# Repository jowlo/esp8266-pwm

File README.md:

# **esp8266-pwm** #
This is only a fork. Everything below is the the original repository's README by [lexszero](https://github.com/lexszero/). It will be kept here until I get around rewriting (parts of) it.
The main goal of this fork is to support multiple PCA9685s on one I2C-line as well as not using MQTT but (if the ESP8266 can handle it) WebSockets for use by a client

All changes to the code and effectively this repository as a whole is under [GPL](https://www.gnu.org/licenses/gpl.txt), whereas lexszeros original code is under WTFPL license (see below).
If i understand the licensing laws correctly, it is allowed to incorporate code released to the Public Domain in... tl;dr. If you disagree, please tell me.)

# Original Readme

## Summary
Code for ESP8266 WiFi module with [NodeMcu firmware](https://github.com/nodemcu/nodemcu-firmware) to control PCA9685 PWM controller. You can easily build WiFi-controlled smart home equipment or toys with this. Also contains a demo application: RGB LED strip with WiFi.

Licensed under [WTFPL](http://www.wtfpl.net/)

## Requirements
### Hardware
- Any ESP8266 module
- PCA9685 connected to ESP's GPIOs

My hardware (so mad skillz!):

_TODO: example schematics, photo/video of actual hardware_

### Software
- [NodeMCU](https://github.com/nodemcu/nodemcu-firmware)
- [esptool](https://github.com/themadinventor/esptool) for flashing NodeMCU
- [luatool](https://github.com/4refr0nt/luatool) for uploading Lua code

## PCA9685 driver Lua API
~~TODO: maybe write something useful here~~

Read the source

There are also some useful stuff in `utils.lua`

## rgbstrip: demo application
Directory `rgbstrip` contains an application to control a RGB LED strip over WiFi via [MQTT protocol](https://en.wikipedia.org/wiki/MQTT). RGB channels are usually driven with MOSFETs controlled by PWM.

### Installation
- Connect ESP8266 to PC (we assume that device is connected to `/dev/ttyUSB0`)
- Install `NodeMCU`, if you don't have one:
```
./esptool/esptool.py --port /dev/ttyUSB0 erase_flash
./esptool/esptool.py --port /dev/ttyUSB0 write_flash 0x0 nodemcu-firmware/pre_build/latest/nodemcu_latest.bin
```
- Edit `rgbstrip/init.lua` and change configuration as you wish
- Upload Lua files
```
for f in pca9685.lua rgbstrip/*.lua; do
    ./luatool/luatool.py -f "$f" -t "`basename $f`" -p /dev/ttyUSB0 || break
done
```
- Pre-compile `pca9685.lua` and `server.lua` on ESP8266. This is needed because `NodeMCU` sometimes runs out of RAM when loading Lua modules. Open your favorite serial terminal program (**warning**: `init.lua` configures UART to 115200 baud, `NodeMCU`'s default is 9600). Run following commands in `NodeMCU` REPL:
```
node.compile('pca9685.lua')
node.compile('server.lua')
```
- If there was a compilation error, you can reset device and try again. Shit happens.
- If compilation was succesfull, there will be created `pca9685.lc` and `server.lc` files in `NodeMCU` filesystem. Now original files can be removed:
```
file.remove('pca9685.lua')
file.remove('server.lua')
```

### MQTT interface
To control RGB strip, publish a MQTT message with topic `<mqtt_topic>/rgb` (where `<mqtt_topic>` is what you set in `init.lua`) and payload with desired color as hex string (e.g. `ff00ff` - purple).

### rgbstrip.sh: a simple control tool
It uses [mosquitto](http://mosquitto.org/) to publish MQTT messages and Xdialog for  simple GUI.
* Set your MQTT credentials in `mqtt_args` variable in the beggining of the script
* Run `rgbstrip.sh` with one of the following arguments
	* `w` or `white`: set total brightness (r=g=b)
	* `c` or `color`: set color with regular color choose dialog
	* `h` or `hsvcolor`: set color with Hue/Saturation/Value sliders
	* `m` or `midi`: read MIDI control events from ALSA and set color accordingly
	* any other value: set color with Red/Green/Blue sliders

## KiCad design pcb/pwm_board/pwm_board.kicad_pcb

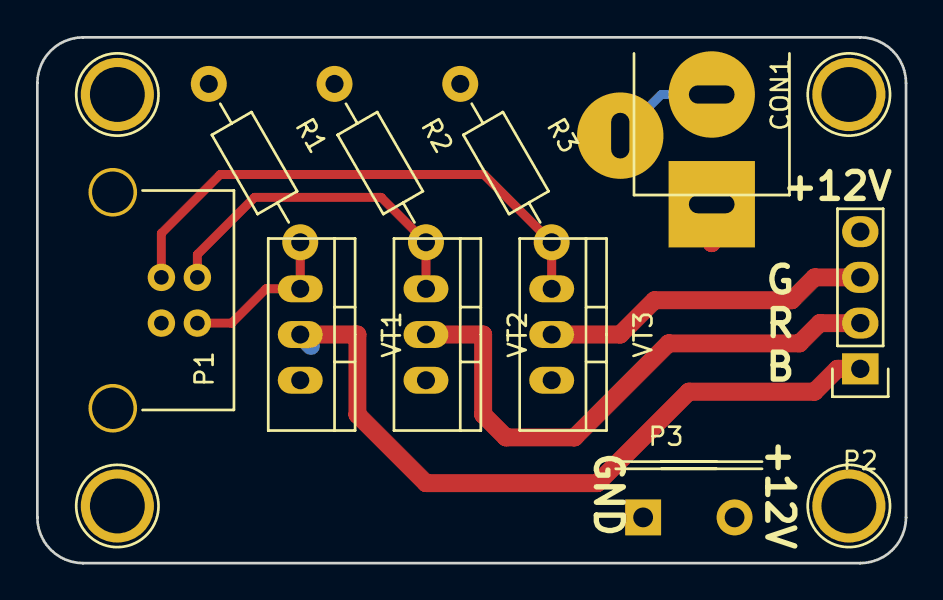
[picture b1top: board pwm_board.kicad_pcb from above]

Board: 2 copper layers, 48.3 x 29.2 mm, 10 parts (0 on the bottom side), 8 nets.

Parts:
CON1: BARREL_JACK; JACK_ALIM
P1: USB_B
P2: CONN_01X04; Pin_Header_Straight_1x04
P3: CONN_01X02; TerminalBlock_Pheonix_MPT-2.54mm_2pol
R1, R2, R3: 10k; Resistor_Horizontal_RM10mm
VT1, VT2, VT3: IRLZ44; TO-220_Neutral123_Vertical

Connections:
Earth: CON1.2, CON1.3, P1.4, P1.5, P3.1, R1.1, R2.1, R3.1, VT1.3, VT2.3, VT3.3
unnamed: CON1.1, P2.4, P3.2
unnamed: P1.1, R1.2, VT1.1
unnamed: P1.2, R2.2, VT2.1
unnamed: P1.3, R3.2, VT3.1
unnamed: P2.1, VT1.2
unnamed: P2.2, VT2.2
unnamed: P2.3, VT3.2

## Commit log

2015-09-22 comments, (try to) optimize i2c-communication, start working on supporting multiple pca9685
2015-09-22 add brightness control
2015-09-24 first working fft
2015-09-24 i guess it works
2015-09-25 adding udpsend
2015-09-25 lots
2015-09-25 pwms and all that
2015-09-25 less noisy terminals
2015-09-25 cleanup
2015-09-26 work on protocol. add 2byte cmd flag. pwm values now 10bit, not 8.
2015-09-28 use native firmware. nodemcu too laggy
2015-09-28 well, there goes my wifi pass. dont try, new one created
2015-09-28 use config.h
2015-09-28 adding settings
2015-10-01 shell
2015-10-01 rename
2015-10-01 file struct cleanup
2015-10-02 gtk gui
2015-10-04 clean working dir
2015-10-04 multi channels
2015-10-04 multiglow
2015-10-04 make flicker work
2015-10-10 start using pca9685 boards
2016-01-02 add python script.
2016-01-03 working python fft. need to logscale binning
2016-01-04 working easyfft
2016-01-04 working fft with many modes. looking good.
2016-01-04 Add init.py for package.
2016-01-05 Add Color include.
2016-01-05 Major refactoring of python sender.
2016-01-05 Let FFT-functions yield states.
2016-01-15 Try new scaling. Move dynamic scaling in fft-class.
2016-01-20 Add first PCB Schematics (and Elecrow-Plots)
2016-02-13 add pwm board discovery and udp beacon
2016-02-13 adding adhoc adaptions
2016-02-13 workaround for pluggable controllers
2016-02-13 adapt color (&correction)
2016-02-21 Add first controller box sketch
2016-02-21 Add stl for github display
2016-02-21 Heighten circle resolution
2016-02-21 Bigger USB-cutouts, fix mounting-holes position
2016-02-21 Add hex nut feet
2016-02-21 Removing edge fills. Not working for 2D-Translation
2016-02-21 Fix pcb thickness
2016-02-22 Add PWM-board box
2016-02-22 Add ctrl-box lasercut SVG
2016-02-22 Add Readme with library link
2016-02-22 Add PWM-Box heat cutouts
2016-02-22 Nicen up PWM-Box heat cutouts for more stability
2016-02-29 Last minute mods
2016-04-25 Add lots, some GUI-Starts
2016-04-25 Lots of work on the gui. Glade file apparantly lost.
2016-04-25 Add Processor Class
2016-04-25 Rebuild glade
2016-04-25 More GUI work
2016-04-26 More GUI work, starts to look nice
2016-06-03 Add dmx to wifi bridge
2016-06-03 30 Channels
2016-06-03 Finish DMX-Bridge
2016-06-14 GUI rework, add grouping, effect chooser
2016-06-15 Add equalizer processor
2016-06-15 Fix errors/warnings. Add FFT-Rescale button
2016-06-15 Fix division by zero
2016-06-15 Automagically find Processors. Parabolic scaling.
2016-06-16 Add strobe stuff
2016-06-17 Rainbow strobe, yeah!
2016-06-17 Remove prints and add HeatEqualizer
2016-06-17 Lots of GUI improvements
2016-06-18 Second day improvements
2016-09-12 DMX Bridge improvements
2016-09-13 Use mDNS(-SD) to discover controller
2016-09-17 Cleanup Arduino sketches
2016-09-17 Add DMX-Modes
2017-07-21 fix things
